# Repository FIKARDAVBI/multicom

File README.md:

- ## Berikut nama-nama calon mahasiswa baru hasil seleksi penerimaan mahasiswa baru gelombang 1 Program Pascasarjana Magister Terapan (S2) PENS Tahun Masuk 2024/2025 :

### 1. Program Studi Teknik Informatika dan Komputer

| **NO** 	| **NOMOR PENDAFTARAN** 	|     **NAMA CALON MAHASISWA**     	|    **PROGRAM STUDI PILIHAN**    	|  **JALUR MASUK**  	|
|:------:	|:---------------------:	|:--------------------------------:	|:-------------------------------:	|:-----------------:	|
|  **1** 	|       2418131001      	|   **MAULANA BINTANG IRFANSYAH**  	| TEKNIK INFORMATIKA DAN KOMPUTER 	| **BEASISWA PENS** 	|
|  **2** 	|       2418131002      	|        **BAHARUDIN HASAN**       	| TEKNIK INFORMATIKA DAN KOMPUTER 	|    **MANDIRI**    	|
|  **3** 	|       2418131003      	| **MUHAMMAD FAUZAN RIZKY AGUSTA** 	| TEKNIK INFORMATIKA DAN KOMPUTER 	|    **MANDIRI**    	|
|  **4** 	|       2418131005      	|             **SANTI**            	| TEKNIK INFORMATIKA DAN KOMPUTER 	| **BEASISWA PENS** 	|
|  **5** 	|       2418131007      	|     **IKBAR ATHALLAH TAUFIK**    	| TEKNIK INFORMATIKA DAN KOMPUTER 	|    **MANDIRI**    	|
|  **6** 	|       2418131008      	|    **GRETA SEPTY PURWIANTONO**   	| TEKNIK INFORMATIKA DAN KOMPUTER 	|    **MANDIRI**    	|
|  **7** 	|       2418131009      	|  **MUHAMMAD INFAN TRI ANDHIKA**  	| TEKNIK INFORMATIKA DAN KOMPUTER 	| **BEASISWA PENS** 	|
|  **8** 	|       2418131011      	|         **WIDI ARROHMAN**        	| TEKNIK INFORMATIKA DAN KOMPUTER 	| **BEASISWA PENS** 	|
|  **9** 	|       2418131012      	|         **AHMAD SIDDIQ**         	| TEKNIK INFORMATIKA DAN KOMPUTER 	| **BEASISWA PENS** 	|
| **10** 	|       2418131014      	|    **WILDAN DHARMA WALIDANIY**   	| TEKNIK INFORMATIKA DAN KOMPUTER 	| **BEASISWA PENS** 	|
| **11** 	|       2418131015      	|   **ASMARALDA LAKSMI FIRDAUSI**  	| TEKNIK INFORMATIKA DAN KOMPUTER 	| **BEASISWA PENS** 	|

----------

### 2. Program Studi Teknik Elektro
| **NO** 	| **NOMOR PENDAFTARAN** 	|     **NAMA CALON MAHASISWA**    	| **PROGRAM STUDI PILIHAN** 	|  **JALUR MASUK**  	|
|:------:	|:---------------------:	|:-------------------------------:	|:-------------------------:	|:-----------------:	|
|  **1** 	|       2418131004      	|   **MUHAMMAD IRFAN TAM TOMO**   	|       TEKNIK ELEKTRO      	|    **MANDIRI**    	|
|  **2** 	|       2418131006      	|    **NADHIFAH SIMTIA AQILAH**   	|       TEKNIK ELEKTRO      	|    **MANDIRI**    	|
|  **3** 	|       2418131010      	|      **BAGAS AJI TIFANTO**      	|       TEKNIK ELEKTRO      	| **BEASISWA PENS** 	|
|  **4** 	|       2418131013      	|     **CANDRA KUSUMA WIJAYA**    	|       TEKNIK ELEKTRO      	| **BEASISWA PENS** 	|
|  **5** 	|       2418131016      	| **NIASY HAYATUL MAKKI AL ARSY** 	|       TEKNIK ELEKTRO      	| **BEASISWA PENS** 	|
|  **6** 	|       2418131017      	|    **RAHMAT MAGHROBI ALWAFI**   	|       TEKNIK ELEKTRO      	| **BEASISWA PENS** 	|

----------

- Berikut terlampir **Surat Keputusan hasil seleksi penerimaan mahasiswa baru gelombang 1 Program Pascasarjana Magister Terapan (S2) PENS Tahun Masuk 2024/2025** :
[SK Penerimaan](https://drive.google.com/file/d/1tZX882sV_TRGg1nzQBjXsqqoMKj0b95t/view?usp=sharing)

- Calon mahasiswa Program Pascasarjana Magister Terapan (S2) PENS yang tertera diatas wajib melakukan Daftar Ulang pada tanggal **17-18 Juni 2024**. Daftar Ulang bisa dilakukan [disini](https://pmb.pens.ac.id/daftarulang/)

- Pembayaran SPP **(bagi yang jalur masuk mandiri)** untuk Semester 1 sebesar **Rp. 9.000.000,-** dilakukan pada tanggal **17-18 Juni 2024**, dan ditunjukkan **bukti pembayaran** via foto / scan ke admin sekretariat pascasarjana PENS pada tanggal **12-13 Agustus 2024(tanggal kegiatan PKKMB).**

- Pelaksanaan kegiatan **Matrikulasi** akan dilakukan **2 Minggu Awal Perkuliahan** dimulai. Untuk informasi jadwal Matrikulasi menyusul.

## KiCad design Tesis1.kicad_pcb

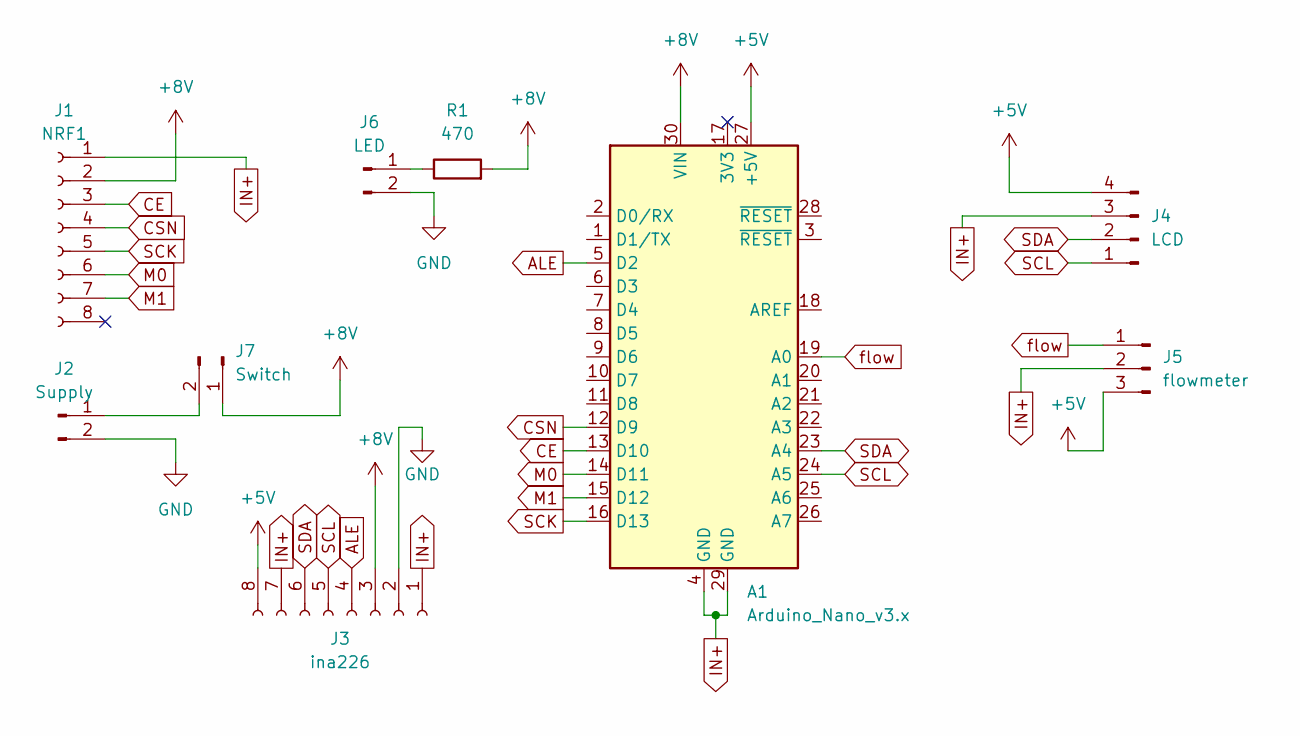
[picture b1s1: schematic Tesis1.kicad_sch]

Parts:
A1: Arduino_Nano_v3.x; Arduino_Nano
J1: NRF1; NRF_adapter
J2: Supply; PinHeader_1x02_P2.54mm_Vertical
J3: ina226; PinHeader_1x08_P2.54mm_Vertical
J4: LCD; JST_EH_B4B-EH-A_1x04_P2.50mm_Vertical
J5: flowmeter; JST_EH_B3B-EH-A_1x03_P2.50mm_Vertical
J6: LED; JST_EH_B2B-EH-A_1x02_P2.50mm_Vertical
J7: Switch; JST_EH_B2B-EH-A_1x02_P2.50mm_Vertical
R1: 470; R_Axial_DIN0204_L3.6mm_D1.6mm_P7.62mm_Horizontal

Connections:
+5V: A1.27 (+5V), J3.8, J4.4, J5.3
+8V: A1.30 (VIN), J1.2, J3.3, J7.1, R1.2
ALE: A1.5 (D2), J3.4
CE: A1.13 (D10), J1.3
CSN: A1.12 (D9), J1.4
GND: J2.2, J3.2, J6.2
IN+: A1.4 (GND), A1.29 (GND), J1.1, J3.1, J3.7, J4.3, J5.2
M0: A1.14 (D11), J1.6
M1: A1.15 (D12), J1.7
unnamed: J2.1, J7.2
unnamed: J6.1, R1.1
SCK: A1.16 (D13), J1.5
SCL: A1.24 (A5), J3.5, J4.1
SDA: A1.23 (A4), J3.6, J4.2
flow: A1.19 (A0), J5.1

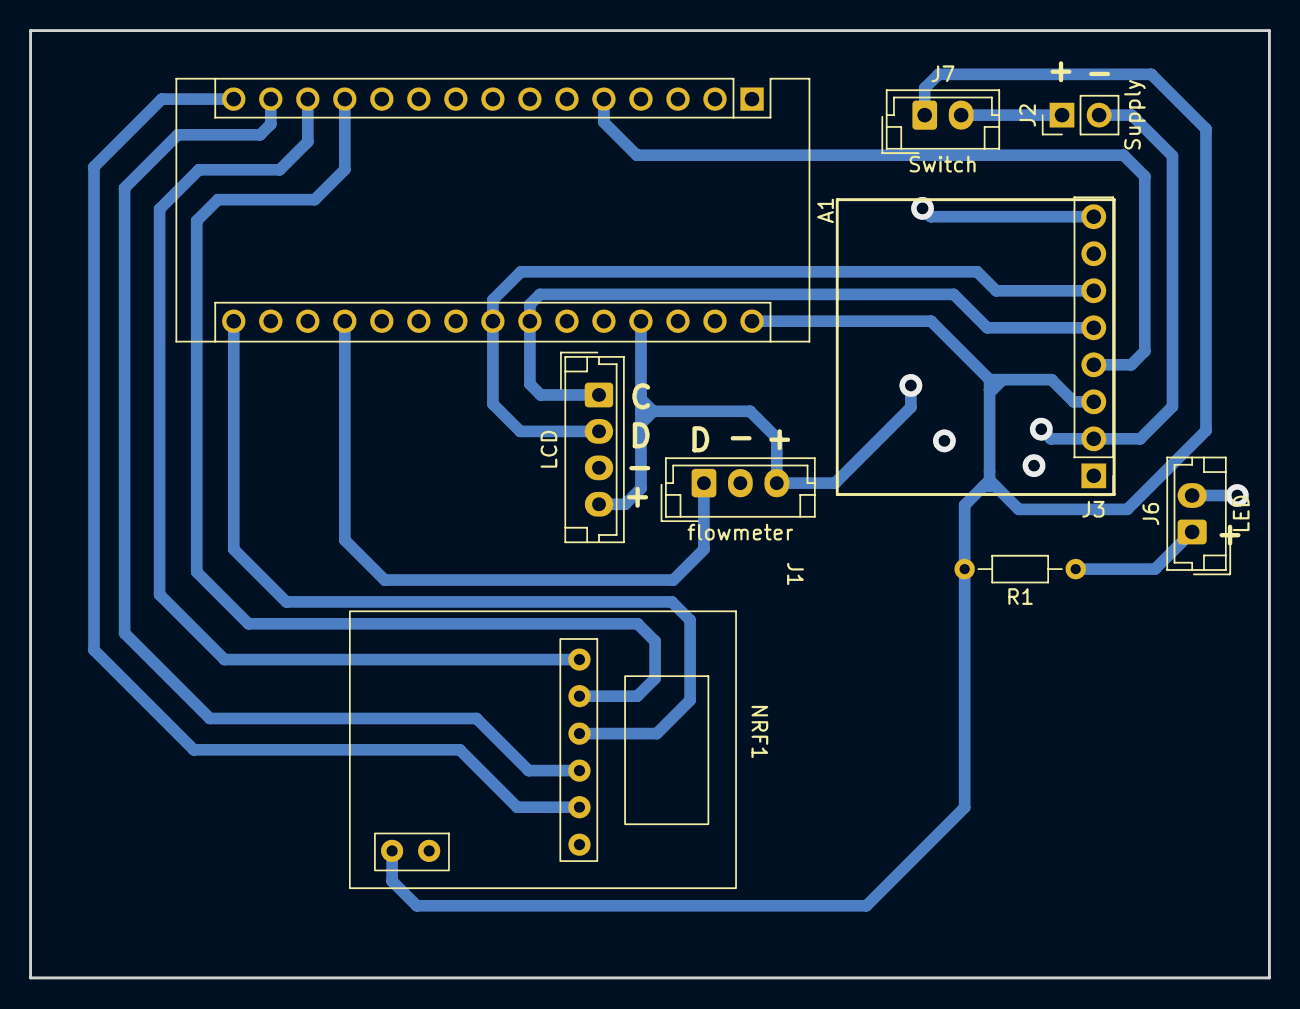
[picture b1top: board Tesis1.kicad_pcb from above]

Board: 2 copper layers, 85.0 x 65.0 mm, 9 parts (0 on the bottom side), 15 nets.

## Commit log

2024-02-01 fix slave5
2024-02-03 add multinode
2024-02-03 add flowmeter sensor
2024-02-05 fix bugs
2024-02-05 fix data coversion bugs
2024-02-05 fix collision between nodes
2024-02-06 add denah pengujian
2024-02-06 fix message buffer in s1 s2 and master
2024-02-06 fix slave issues with message buffer
2024-02-08 fix issues in the B protocol format
2024-02-08 add LNA enable
2024-03-27 add transmission time testing
